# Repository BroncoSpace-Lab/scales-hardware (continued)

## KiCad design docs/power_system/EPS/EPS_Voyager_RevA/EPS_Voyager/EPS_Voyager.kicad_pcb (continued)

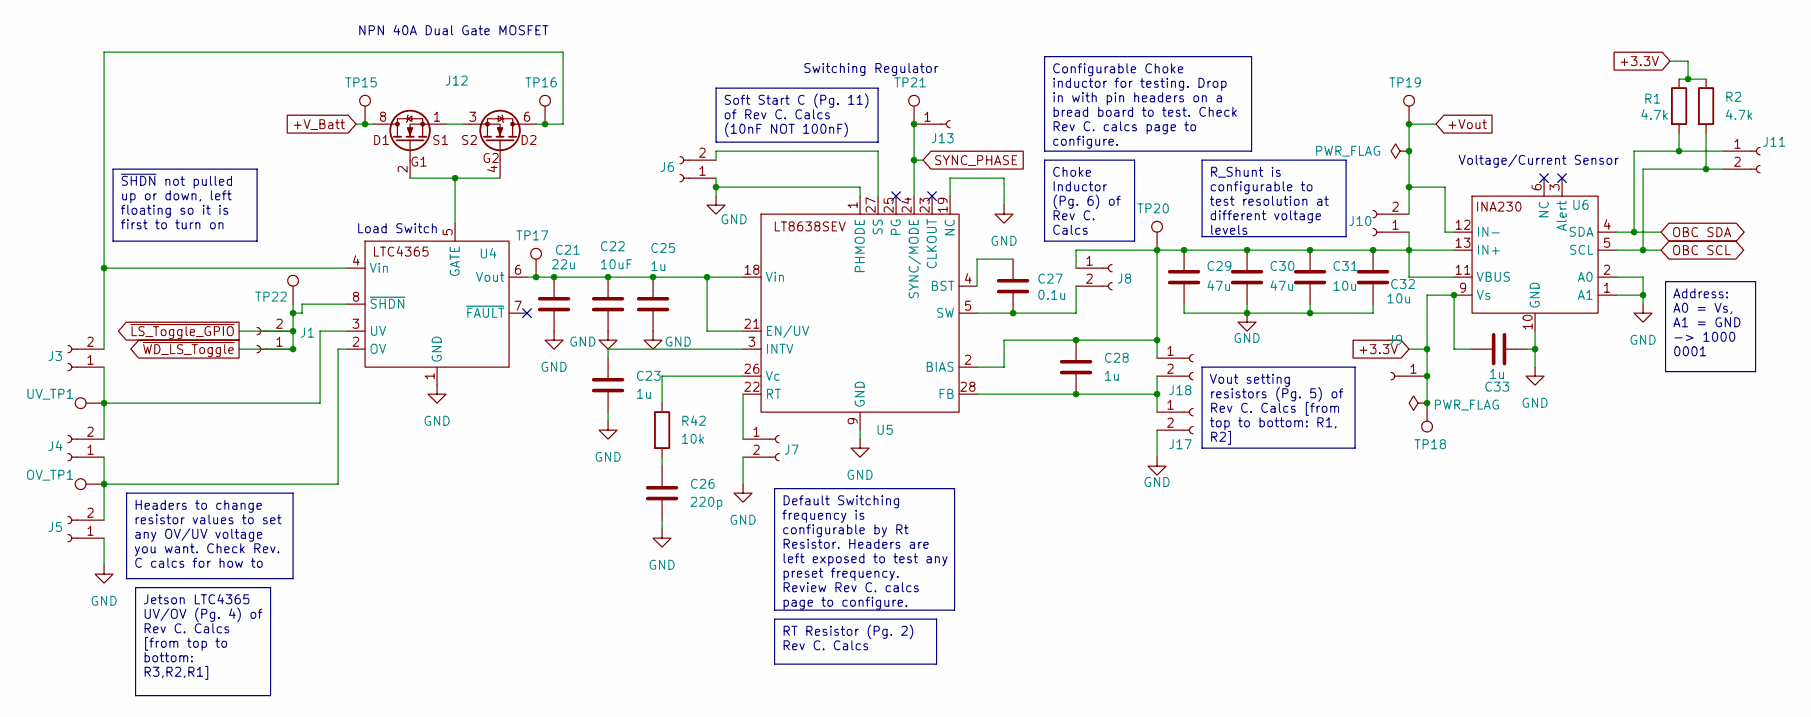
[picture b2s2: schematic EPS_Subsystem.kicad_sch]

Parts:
C21: 22u; C_1210_3225Metric
C22: 10uF; C_1210_3225Metric
C23, C25, C28, C33: 1u; C_1210_3225Metric
C26: 220p; C_1210_3225Metric
C27: 0.1u; C_1210_3225Metric
C29, C30: 47u; C_1210_3225Metric
C31, C32: 10u; C_1210_3225Metric
J1, J3, J4, J5, J6, J7, J8, J10, J11, J17, J18: Conn_01x02_Socket; PinSocket_1x02_P2.54mm_Vertical
J9, J13: Conn_01x01_Socket; PinSocket_1x01_P2.54mm_Vertical
J12: SISB46DN-T1-GE3
OV_TP1: TestPoint; TestPoint_Pad_1.0x1.0mm
R1, R2: 4.7k; R_0603_1608Metric
R42: 10k; R_0603_1608Metric
TP15, TP16, TP17, TP18, TP19, TP20, TP21, TP22: TestPoint; TestPoint_Pad_1.0x1.0mm
U4: LTC4365
U5: LT8638SEVPBF
U6: INA230; INA230AIRGTT
UV_TP1: TestPoint; TestPoint_Pad_1.0x1.0mm

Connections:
+3.3V: C33.2, J9.1, R1.1, R2.1, TP18.1, U6.9 (Vs); also elsewhere on the board
+V_Batt: J12.7, J12.8, TP15.1; also elsewhere on the board
+Vout: J10.2, TP19.1, U6.12 (IN-)
GND: C21.2, C22.2, C23.2, C25.2, C26.2, C29.2, C30.2, C31.2, C32.2, C33.1, J5.1, J6.1, J7.2, J17.2, U4.1 (GND), U5.1 (PHMODE), U5.9 (GND), U5.19 (NC), U6.1 (A1), U6.2 (A0), U6.10 (GND); also elsewhere on the board
unnamed: C26.1, R42.2
unnamed: J3.1, J4.2, U4.3 (UV), UV_TP1.1
unnamed: J3.2, J12.5, J12.6, TP16.1, U4.4 (Vin)
unnamed: J4.1, J5.2, OV_TP1.1, U4.2 (OV)
unnamed: J6.2, U5.27 (SS)
unnamed: J7.1, U5.22 (RT)
unnamed: C27.2, J8.2, U5.5 (SW)
unnamed: C28.1, C29.1, C30.1, C31.1, C32.1, J8.1, J10.1, J18.1, TP20.1, U5.2 (BIAS), U6.11 (VBUS), U6.13 (IN+)
unnamed: J12.1, J12.3
unnamed: C28.2, J17.1, J18.2, U5.28 (FB)
unnamed: J12.2, J12.4, U4.5 (GATE)
unnamed: C21.1, C22.1, C25.1, TP17.1, U4.6 (Vout), U5.18 (Vin), U5.21 (EN/UV)
unnamed: C27.1, U5.4 (BST)
unnamed: C23.1, U5.3 (INTV)
unnamed: R42.1, U5.26 (Vc)
OBC SCL: J11.2, R2.2, U6.5 (SCL)
OBC SDA: J11.1, R1.2, U6.4 (SDA)
SYNC_PHASE: J13.1, TP21.1, U5.24 (SYNC/MODE)
~LS_Toggle_GPIO: J1.1, J1.2, TP22.1, U4.8 (~SHDN)

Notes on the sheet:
Switching Regulator
NPN 40A Dual Gate MOSFET
Voltage/Current Sensor
Load Switch
RT Resistor (Pg. 2) Rev C. Calcs
Soft Start C (Pg. 11) of Rev C. Calcs (10nF NOT 100nF)
Headers to change resistor values to set any OV/UV voltage you want. Check Rev. C calcs for how to
R_Shunt is configurable to test resolution at different voltage levels
Configurable Choke inductor for testing. Drop in with pin headers on a bread board to test. Check Rev C. calcs page to configure.
Address: A0 = Vs, A1 = GND -> 1000 0001
Vout setting resistors (Pg. 5) of Rev C. Calcs [from top to bottom: R1, R2]
Choke Inductor (Pg. 6) of Rev C. Calcs
Jetson LTC4365 UV/OV (Pg. 4) of Rev C. Calcs [from top to bottom: R3,R2,R1]
~{SHDN} not pulled up or down, left floating so it is first to turn on
Default Switching frequency is configurable by Rt Resistor. Headers are left exposed to test any preset frequency. Review Rev C. calcs page to configure.

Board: 4 copper layers, 52 parts (0 on the bottom side), 29 nets, no tracks yet.

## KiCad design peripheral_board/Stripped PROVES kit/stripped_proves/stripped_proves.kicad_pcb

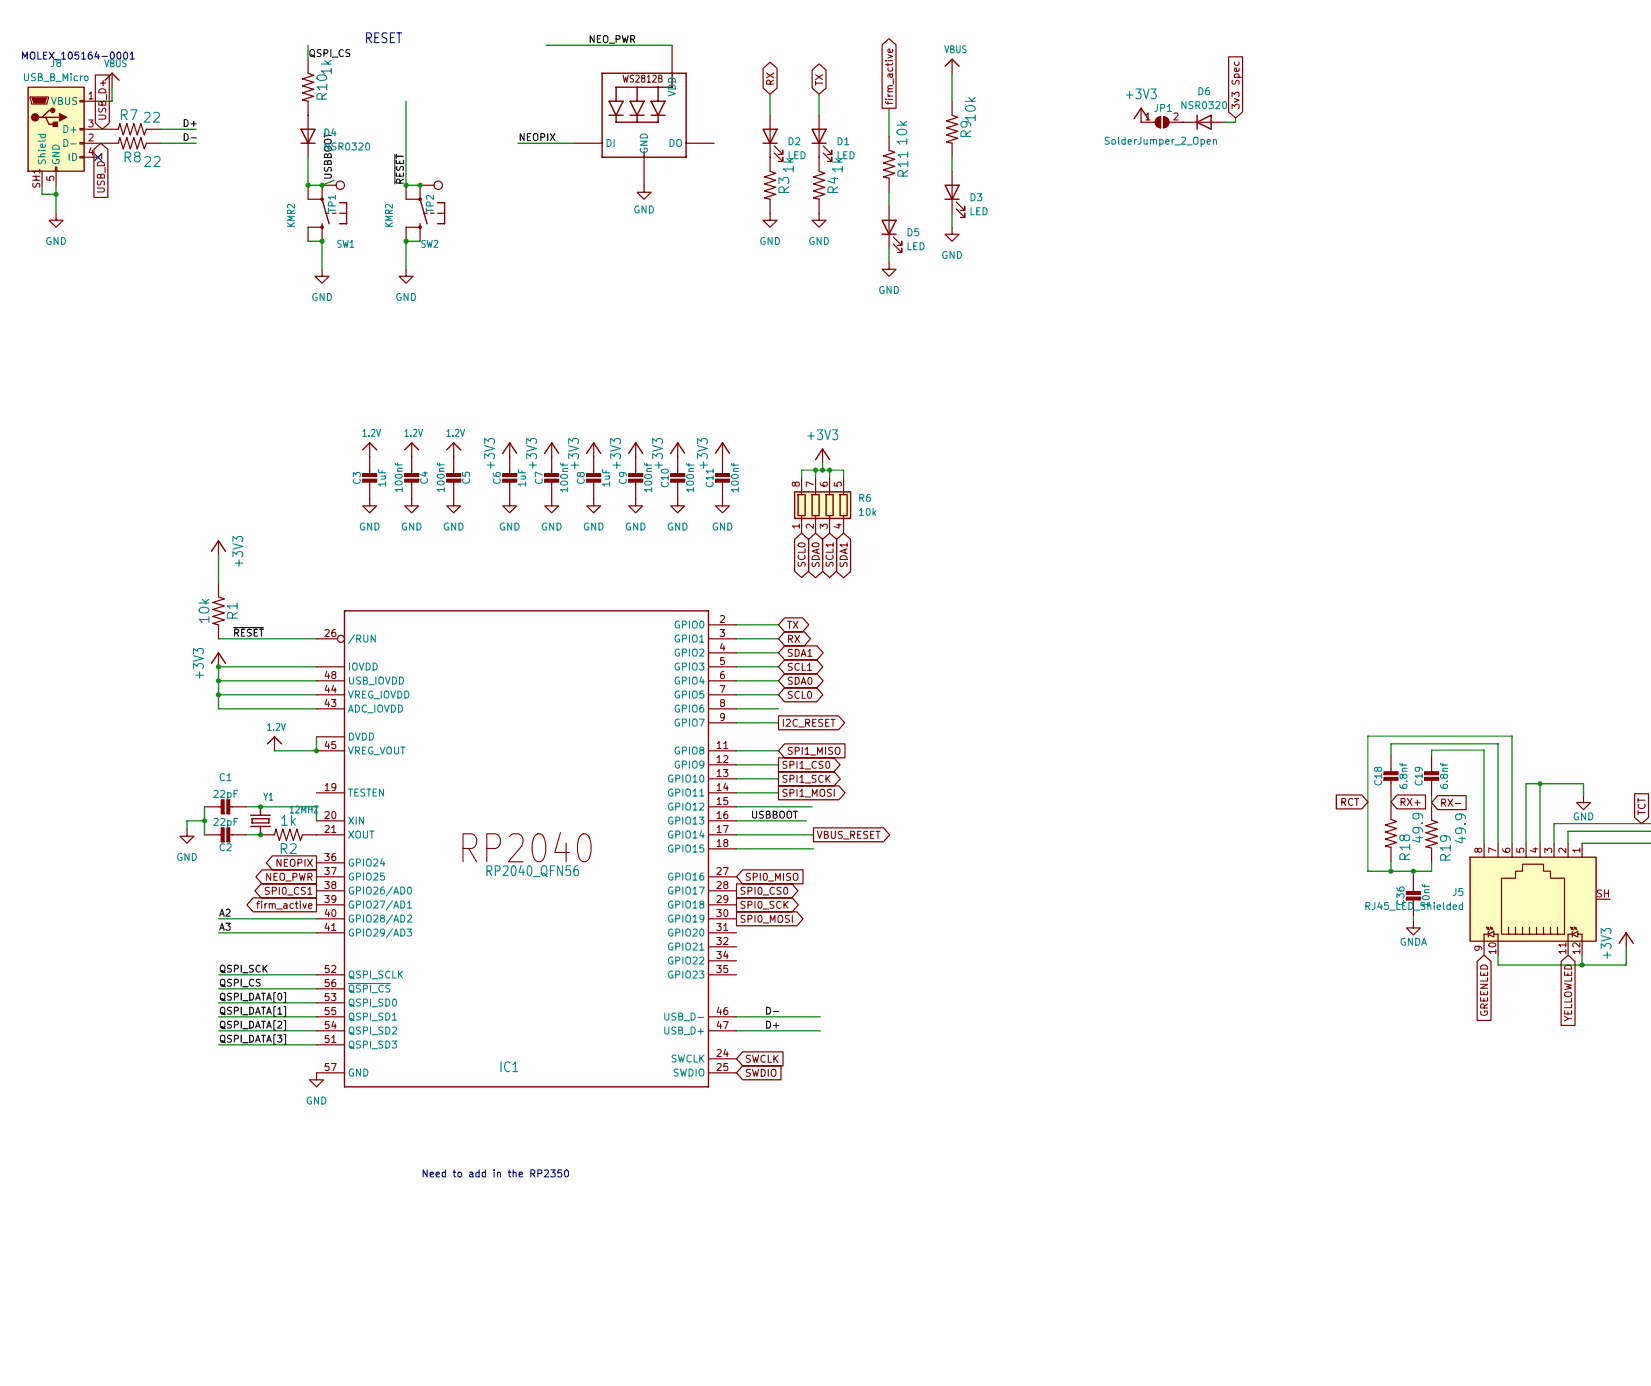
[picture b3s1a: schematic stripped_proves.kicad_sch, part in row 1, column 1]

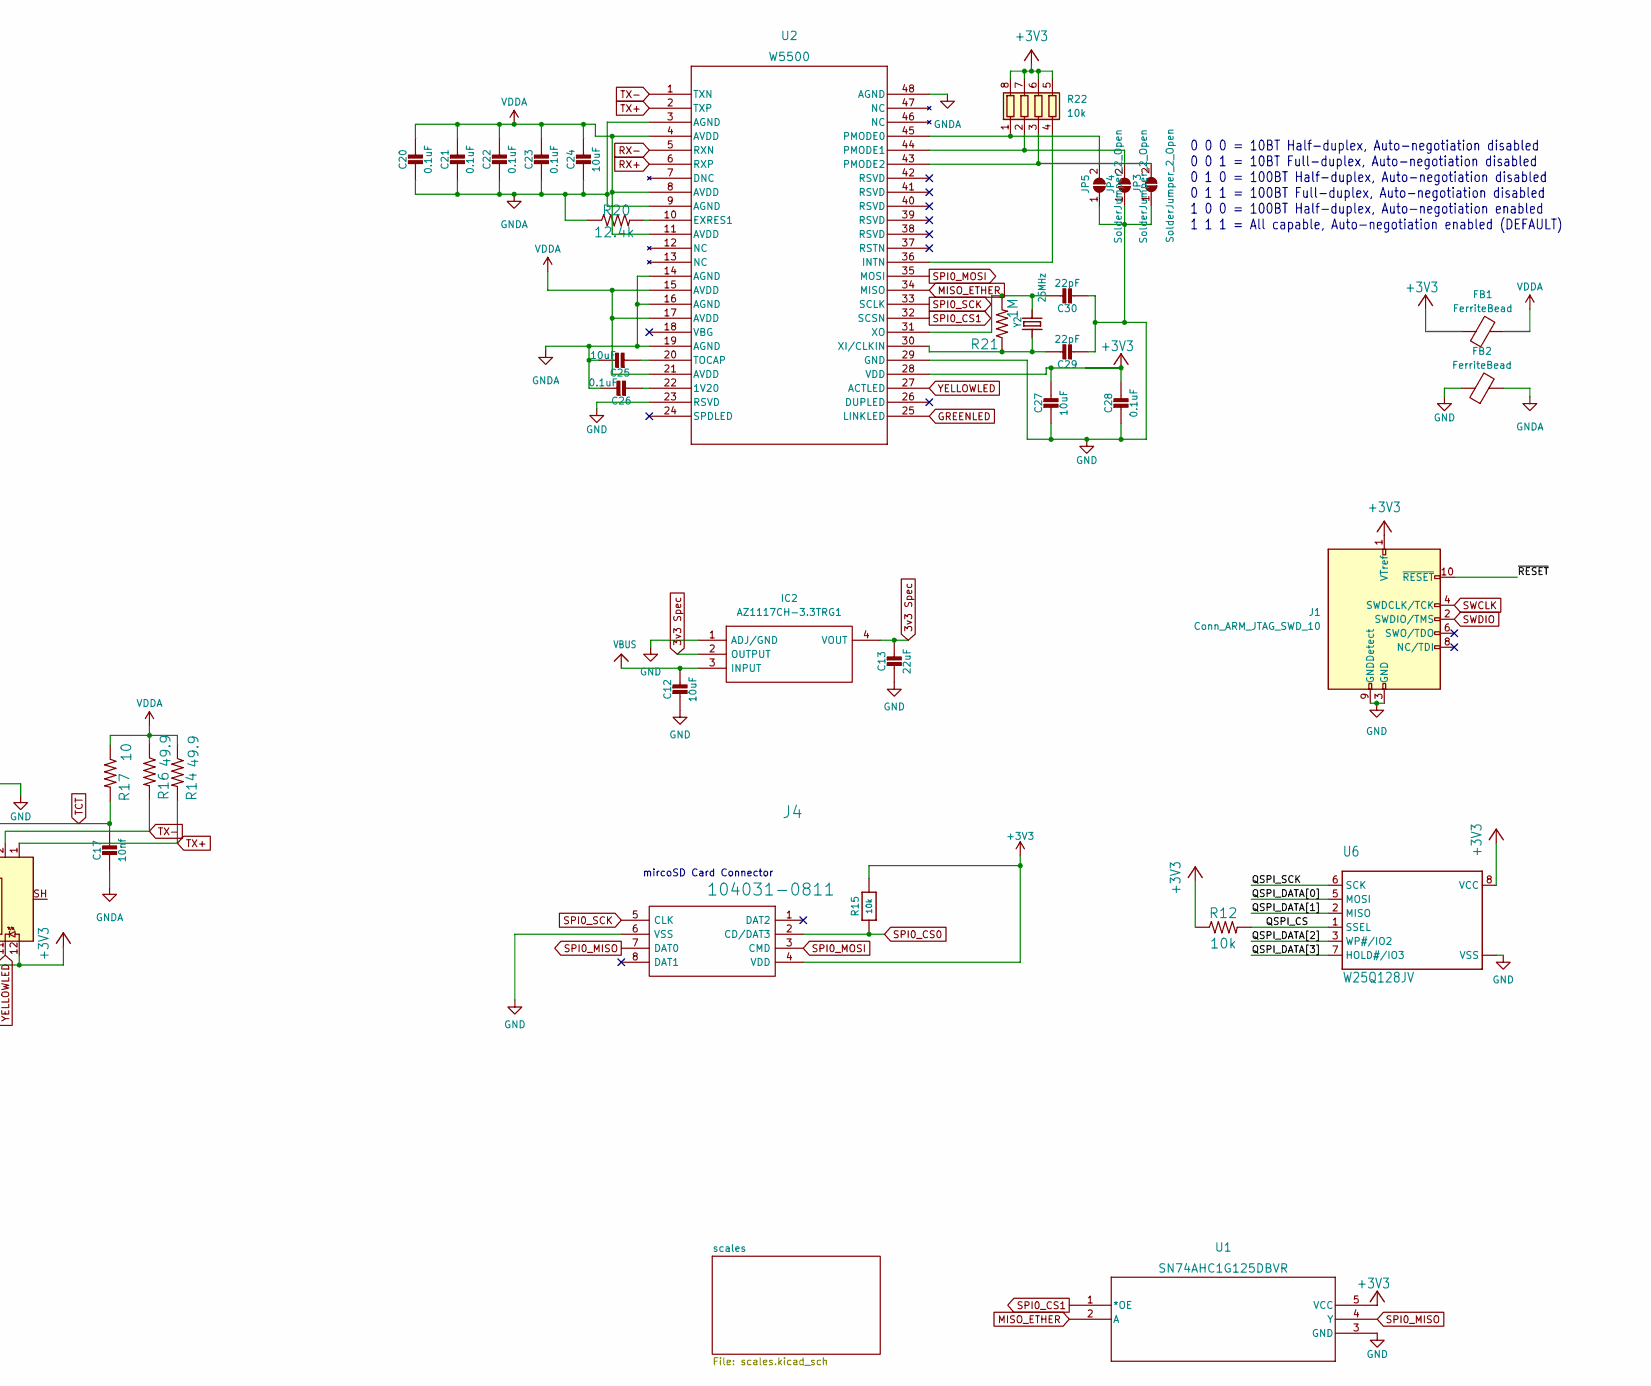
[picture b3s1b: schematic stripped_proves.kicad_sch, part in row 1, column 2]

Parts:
C1, C2, C29, C30: 22pF; C_0402_1005Metric
C3, C6, C8: 1uF; C_0603_1608Metric
C4, C5, C7, C9, C10, C11: 100nf; C_0402_1005Metric
C12: 10uF; C_0603_1608Metric
C13: 22uF; C_0603_1608Metric
C17, C36: 10nf; C_0402_1005Metric
C18, C19: 6.8nf; C_0402_1005Metric
C20, C21, C22, C23, C26, C28: 0.1uF; C_0603_1608Metric
C24, C25, C27: 10uF; C_0805_2012Metric
D1, D2, D3, D5: LED; LED_0603_1608Metric
D4, D6: NSR0320; D_SOD-323F
FB1, FB2: FerriteBead; R_0603_1608Metric
IC1: RP2040_QFN56; QFN-56-1EP_7x7mm_P0.4mm_EP3.2x3.2mm_ThermalVias
IC2: AZ1117CH-3.3TRG1; SOT-223; Mouser Part Number 621-AZ1117CH-3.3TRG1
J1: Conn_ARM_JTAG_SWD_10; JTAG_2X05_1.27MM_BOX_NOCREAM
J4: 104031-0811; microSD_HC_Molex_104031-0811; Manufacturer_Part_Number 104031-0811; Mouser Part Number 538-104031-0811
J5: RJ45_LED_Shielded; RB1-125BAG1A_WIZ
J8: USB_B_Micro; MOLEX_105164-0001
JP1, JP3, JP4, JP5: SolderJumper_2_Open; SolderJumper-2_P1.3mm_Open_RoundedPad1.0x1.5mm
LED1: WS2812B_SK6812_1515; LED_WS2812B_PLCC4_5.0x5.0mm_P3.2mm
R1, R9, R11, R12: 10k; R_0603_1608Metric
R2: 1k; R_0402_1005Metric
R3, R4, R10: 1k; R_0603_1608Metric
R6, R22: 10k; R_Array_Convex_4x0603
R7, R8: 22; R_0603_1608Metric
R14, R16, R18, R19: 49.9; R_0603_1608Metric
R15: 10k; R_0402_1005Metric
R17: 10; R_0603_1608Metric
R20: 12.4k; R_0603_1608Metric
R21: 1M; R_0603_1608Metric
SW1, SW2: KMR2; BTN_KMR2_4.6X2.8
TP1: USBBOOT; TestPoint_Loop_D1.80mm_Drill1.0mm_Beaded
TP2: RESET; TestPoint_Loop_D1.80mm_Drill1.0mm_Beaded
U1: SN74AHC1G125DBVR; SOT-23-5
U2: W5500; LQFP-48_7x7mm_P0.5mm
U6: W25Q128JV; SOIC-8_5.275x5.275mm_P1.27mm
Y1: 12MHZ; Crystal_SMD_2520-4Pin_2.5x2.0mm
Y2: 25MHz; Crystal_SMD_3225-4Pin_3.2x2.5mm

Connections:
1.2V: C3.1, C4.2, C5.2, IC1.23 (DVDD), IC1.45 (VREG_VOUT), IC1.50 (DVDD)
3v3 Spec: C13.1, D6.2 (A), IC2.2 (OUTPUT), IC2.4 (VOUT)
+3V3: C6.1, C7.1, C8.1, C9.1, C10.1, C11.1, C27.1, C28.1, FB1.1, IC1.1 (IOVDD), IC1.10 (IOVDD), IC1.22 (IOVDD), IC1.33 (IOVDD), IC1.42 (IOVDD), IC1.43 (ADC_IOVDD), IC1.44 (VREG_IOVDD), IC1.48 (USB_IOVDD), IC1.49 (IOVDD), J1.1 (VTref), J4.4 (VDD), J5.10, J5.12, JP1.1 (A), R1.1, R6.5 (R4.2), R6.6 (R3.2), R6.7 (R2.2), R6.8 (R1.2), R12.1, R15.2, R22.5 (R4.2), R22.6 (R3.2), R22.7 (R2.2), R22.8 (R1.2), U1.5 (VCC), U2.28 (VDD), U6.8 (VCC); also elsewhere on the board
/A2: IC1.40 (GPIO28/AD2)
/A3: IC1.41 (GPIO29/AD3)
/D+: IC1.47 (USB_D+), R7.1
/D-: IC1.46 (USB_D-), R8.1
/QSPI_CS: IC1.56 (~QSPI_CS), R10.1, R12.2, U6.1 (SSEL)
/QSPI_DATA[0]: IC1.53 (QSPI_SD0), U6.5 (MOSI)
/QSPI_DATA[1]: IC1.55 (QSPI_SD1), U6.2 (MISO)
/QSPI_DATA[2]: IC1.54 (QSPI_SD2), U6.3 (WP#/IO2)
/QSPI_DATA[3]: IC1.51 (QSPI_SD3), U6.7 (HOLD#/IO3)
/QSPI_SCK: IC1.52 (QSPI_SCLK), U6.6 (SCK)
/USBBOOT: D4.1 (K), IC1.16 (GPIO13), SW1.A, SW1.A' (P1), TP1.1
/~RESET: IC1.26 (/RUN), J1.10 (~RESET), R1.2, SW2.A, SW2.A' (P1), TP2.1
EN_1.2V: C12.1, IC2.3 (INPUT), J8.1 (VBUS), R9.1; also elsewhere on the board
GND: C1.1, C2.1, C3.2, C4.1, C5.1, C6.2, C7.2, C8.2, C9.2, C10.2, C11.2, C12.2, C13.2, C27.2, C28.2, C29.2, C30.2, D3.1 (K), D5.1 (K), FB2.1, IC1.57 (GND), IC2.1 (ADJ/GND), J1.3 (GND), J1.5 (GND), J1.9 (GNDDetect), J4.6 (VSS), J5.4, J5.5, J8.5 (GND), J8.SH1 (Shield), LED1.3 (GND), R3.2, R4.2, SW1.B (S), SW1.B' (S1), SW2.B (S), SW2.B' (S1), U1.3 (GND), U2.23 (RSVD), U2.29 (GND), U6.4 (VSS), U6.PAD (VSS); also elsewhere on the board
GNDA: C17.2, C20.2, C21.2, C22.2, C23.2, C24.2, C25.1, C26.1, C36.2, FB2.2, R20.1, U2.3 (AGND), U2.9 (AGND), U2.14 (AGND), U2.16 (AGND), U2.19 (AGND), U2.48 (AGND)
GREENLED: J5.9, U2.25 (LINKLED)
I2C_RESET: IC1.9 (GPIO7)
MISO_ETHER: U1.2 (A), U2.34 (MISO)
NEOPIX: IC1.36 (GPIO24), LED1.4 (DI)
NEO_PWR: IC1.37 (GPIO25), LED1.1 (VDD)
unnamed: C2.2, R2.2, Y1.1
unnamed: C18.1, J5.7
unnamed: C19.1, J5.8
unnamed: D1.1 (K), R4.1
unnamed: D2.1 (K), R3.1
unnamed: D3.2 (A), R9.2
unnamed: D4.2 (A), R10.2
unnamed: D5.2 (A), R11.2
unnamed: D6.1 (K), JP1.2 (B)
unnamed: C1.2, IC1.20 (XIN), Y1.3 (2)
unnamed: IC1.21 (XOUT), R2.1
unnamed: JP3.1 (A), JP4.1 (A), JP5.1 (A)
unnamed: JP3.2 (B), R22.3 (R3.1), U2.43 (PMODE2)
unnamed: JP4.2 (B), R22.2 (R2.1), U2.44 (PMODE1)
unnamed: JP5.2 (B), R22.1 (R1.1), U2.45 (PMODE0)
unnamed: R22.4 (R4.1), U2.36 (INTN)
unnamed: C26.2, U2.22 (1V20)
unnamed: R20.2, U2.10 (EXRES1)
unnamed: C25.2, U2.20 (TOCAP)
unnamed: C29.1, R21.1, U2.30 (XI/CLKIN), Y2.1
unnamed: C30.1, R21.2, U2.31 (XO), Y2.3 (2)
RCT: C36.1, J5.6, R18.2, R19.2
RX: D2.2 (A), IC1.3 (GPIO1)
RX+: C18.2, R18.1, U2.6 (RXP)
RX-: C19.2, R19.1, U2.5 (RXN)
SCL0: IC1.7 (GPIO5), R6.1 (R1.1)
SCL1: IC1.5 (GPIO3), R6.3 (R3.1)
SDA0: IC1.6 (GPIO4), R6.2 (R2.1)
SDA1: IC1.4 (GPIO2), R6.4 (R4.1)
SPI0_CS0: IC1.28 (GPIO17), J4.2 (CD/DAT3), R15.1
SPI0_CS1: IC1.38 (GPIO26/AD0), U1.1 (*OE), U2.32 (SCSN)
SPI0_MISO: IC1.27 (GPIO16), J4.7 (DAT0), U1.4 (Y)
SPI0_MOSI: IC1.30 (GPIO19), J4.3 (CMD), U2.35 (MOSI)
SPI0_SCK: IC1.29 (GPIO18), J4.5 (CLK), U2.33 (SCLK)
SPI1_CS0: IC1.12 (GPIO9)
SPI1_MISO: IC1.11 (GPIO8)
SPI1_MOSI: IC1.14 (GPIO11)
SPI1_SCK: IC1.13 (GPIO10)
SWCLK: IC1.24 (SWCLK), J1.4 (SWDCLK/TCK)
SWDIO: IC1.25 (SWDIO), J1.2 (SWDIO/TMS)
TCT: C17.1, J5.3, R17.2
TX: D1.2 (A), IC1.2 (GPIO0)
TX+: J5.1, R14.2, U2.2 (TXP)
TX-: J5.2, R16.2, U2.1 (TXN)
USB_D+: J8.3 (D+), R7.2
USB_D-: J8.2 (D-), R8.2
VBUS_RESET: IC1.17 (GPIO14)
VDDA: C20.1, C21.1, C22.1, C23.1, C24.1, FB1.2, R14.1, R16.1, R17.1, U2.4 (AVDD), U2.8 (AVDD), U2.11 (AVDD), U2.15 (AVDD), U2.17 (AVDD), U2.21 (AVDD)
YELLOWLED: J5.11, U2.27 (ACTLED)
firm_active: IC1.39 (GPIO27/AD1), R11.1

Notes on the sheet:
0 0 0 = 10BT Half-duplex, Auto-negotiation disabled 0 0 1 = 10BT Full-duplex, Auto-negotiation disabled 0 1 0 = 100BT Half-duplex, Auto-negotiation disabled 0 1 1 = 100BT Full-duplex, Auto-negotiation disabled 1 0 0 = 100BT Half-duplex, Auto-negotiation enabled 1 1 1 = All capable, Auto-negotiation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
mircoSD Card Connector
MOLEX_105164-0001
RESET
Need to add in the RP2350

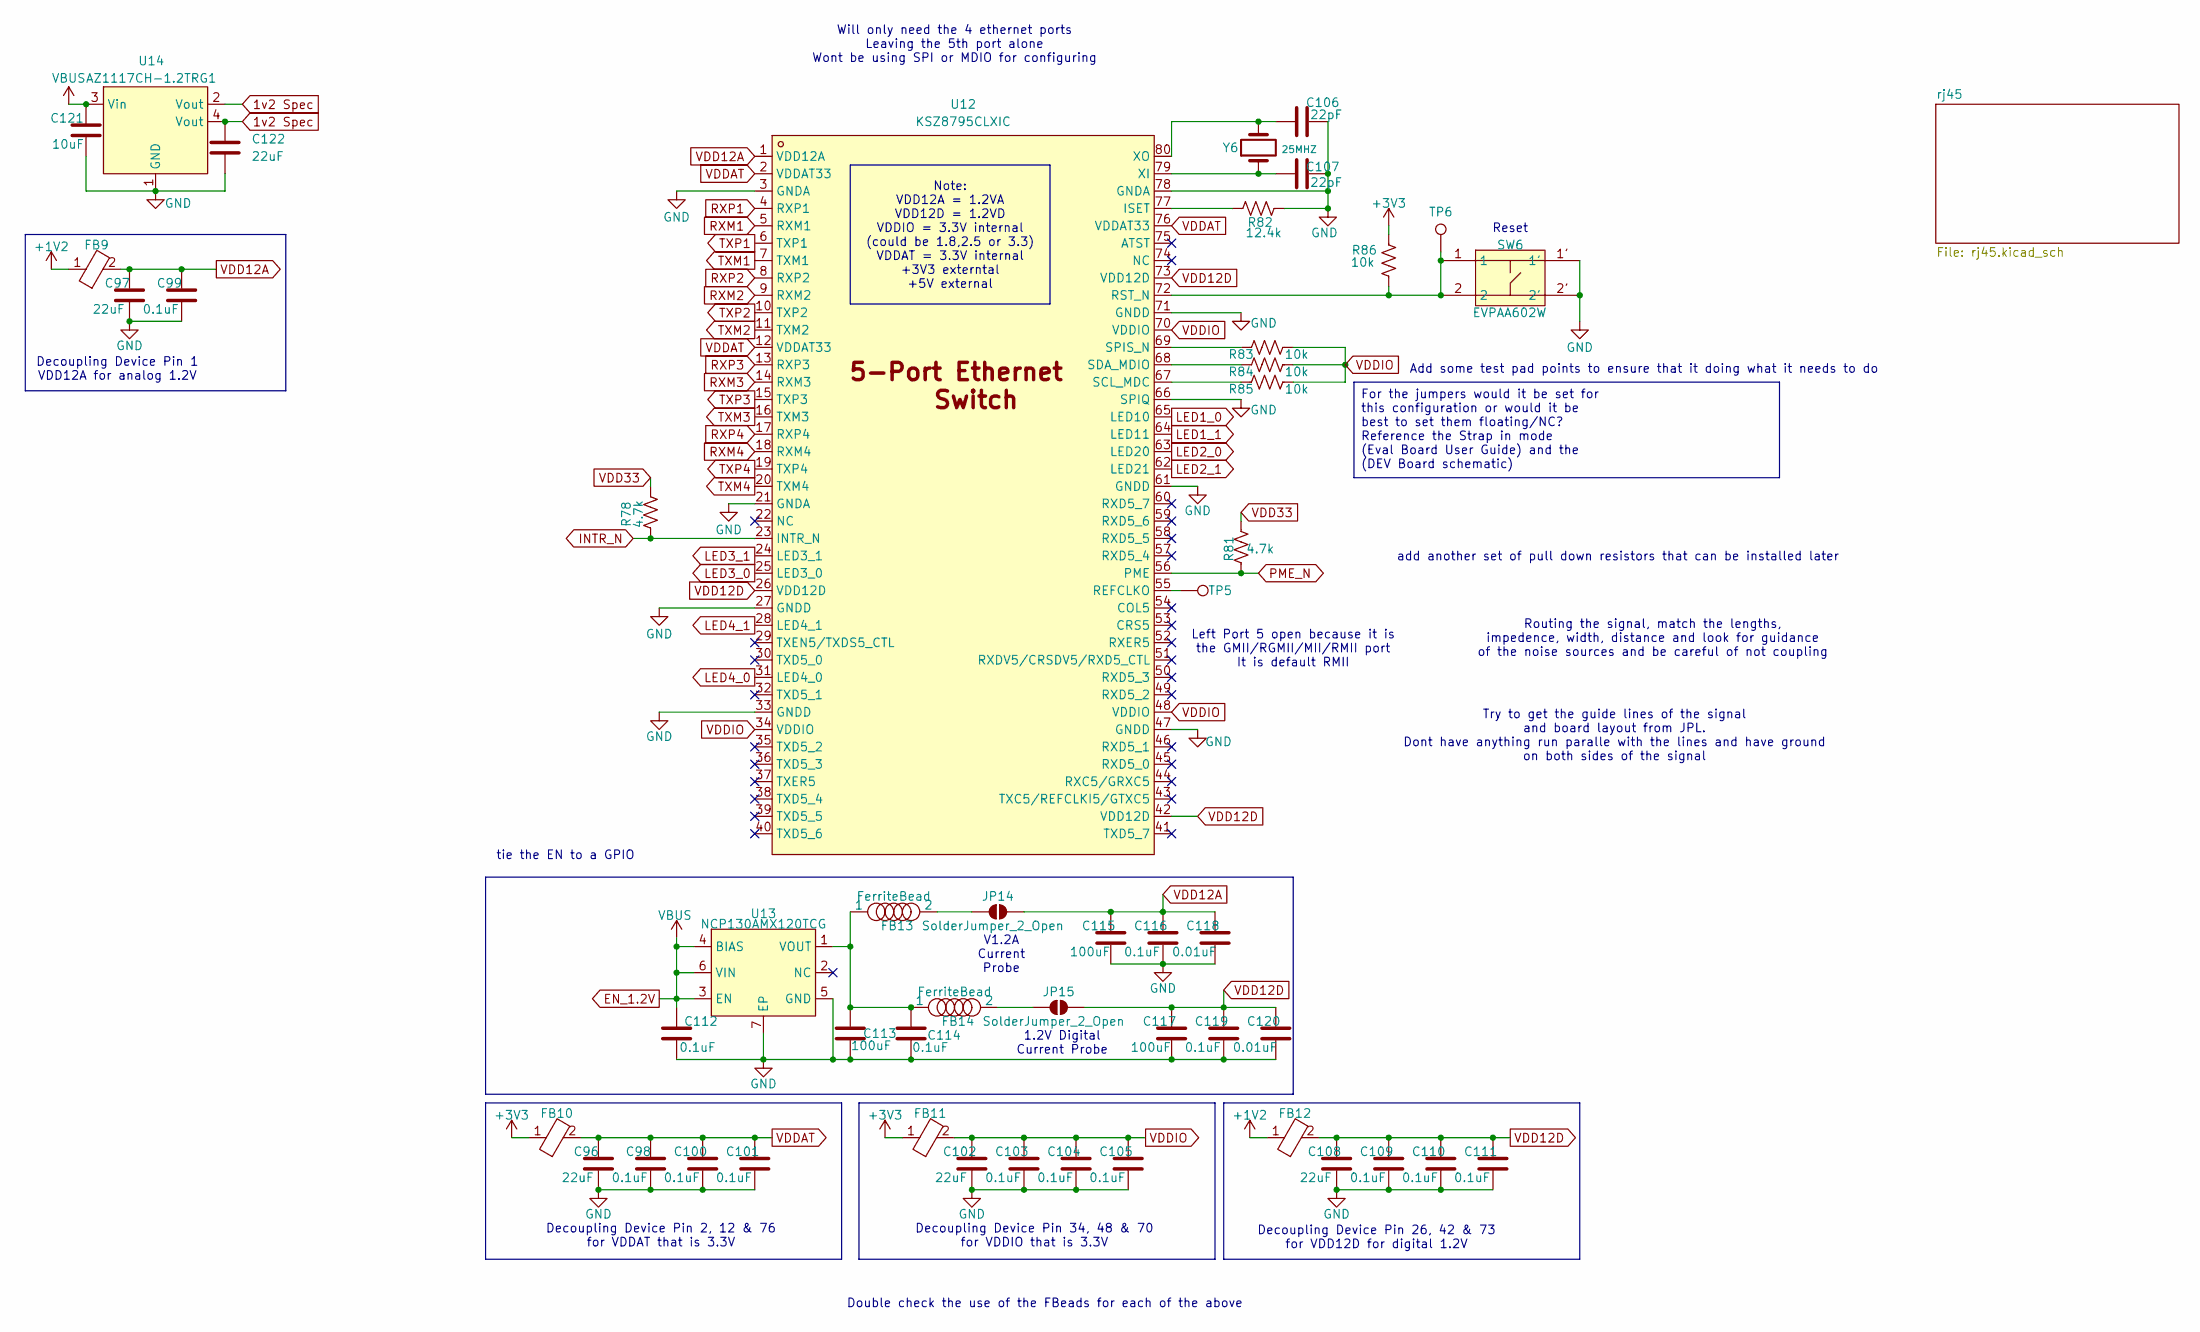
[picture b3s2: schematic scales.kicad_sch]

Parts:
C96, C97, C102, C108, C122: 22uF; C_0402_1005Metric
C98, C99, C100, C101, C103, C104, C105, C109, C110, C111, C112, C114, C116, C119: 0.1uF; C_0402_1005Metric
C106, C107: 22pF; C_0402_1005Metric
C113, C115, C117: 100uF; C_0402_1005Metric
C118, C120: 0.01uF; C_0402_1005Metric
C121: 10uF; C_0402_1005Metric
FB9, FB10, FB11, FB12: CBW321609U101T; L1206; LCSC Part C91466
FB13, FB14: FerriteBead; L_0603_1608Metric
JP14, JP15: SolderJumper_2_Open; SolderJumper-2_P1.3mm_Open_RoundedPad1.0x1.5mm
R78, R81: 4.7k; R_0603_1608Metric
R82: 12.4k; R_0603_1608Metric
R83, R84, R85, R86: 10k; R_0603_1608Metric
SW6: EVPAA602W; KEY-TH_4P-L3.5-W4.9-P2.80-LS4.3; LCSC Part C79148
TP5, TP6: TestPoint; TestPoint_Pad_1.0x1.0mm
U12: KSZ8795CLXIC; LQFP-80_L10.0-W10.0-P0.40-LS12.2-BL; LCSC Part C69416
U13: NCP130AMX120TCG; XDFN-6_L1.2-W1.2-P0.40-BL-EP; LCSC Part C892096
U14: AZ1117CH-1.2TRG1; SOT-223-3_L6.5-W3.4-P2.30-LS7.0-BR; LCSC Part C507895
Y6: 25MHZ; Crystal_SMD_2012-2Pin_2.0x1.2mm

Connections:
1v2 Spec: C122.2, U14.2 (Vout), U14.4 (Vout)
+1V2: FB9.1, FB12.1
+3V3: FB10.1, FB11.1, R86.1; also elsewhere on the board
EN_1.2V: C112.2, C121.2, U13.3 (EN), U13.4 (BIAS), U13.6 (VIN), U14.3 (Vin); also elsewhere on the board
GND: C96.1, C97.1, C98.1, C99.1, C100.1, C101.1, C102.1, C103.1, C104.1, C105.1, C106.2, C107.2, C108.1, C109.1, C110.1, C111.1, C112.1, C113.1, C114.1, C115.1, C116.1, C117.1, C118.1, C119.1, C120.1, C121.1, C122.1, R82.2, SW6.1', SW6.2', U12.3 (GNDA), U12.21 (GNDA), U12.27 (GNDD), U12.33 (GNDD), U12.47 (GNDD), U12.61 (GNDD), U12.66 (SPIQ), U12.71 (GNDD), U12.78 (GNDA), U13.5 (GND), U13.7 (EP), U14.1 (GND); also elsewhere on the board
INTR_N: R78.2, U12.23 (INTR_N)
LED1_0: U12.65 (LED10)
LED1_1: U12.64 (LED11)
LED2_0: U12.63 (LED20)
LED2_1: U12.62 (LED21)
LED3_0: U12.25 (LED3_0)
LED3_1: U12.24 (LED3_1)
LED4_0: U12.31 (LED4_0)
LED4_1: U12.28 (LED4_1)
unnamed: FB13.2, JP14.2 (B)
unnamed: FB14.2, JP15.2 (B)
unnamed: R82.1, U12.77 (ISET)
unnamed: TP5.1, U12.55 (REFCLKO)
unnamed: R86.2, SW6.1, SW6.2, TP6.1, U12.72 (RST_N)
unnamed: R85.1, U12.67 (SCL_MDC)
unnamed: R84.1, U12.68 (SDA_MDIO)
unnamed: R83.1, U12.69 (SPIS_N)
unnamed: C107.1, U12.79 (XI), Y6.1
unnamed: C106.1, U12.80 (XO), Y6.2
unnamed: C113.2, C114.2, FB13.1, FB14.1, U13.1 (VOUT)
PME_N: R81.2, U12.56 (PME)
RXM1: U12.5 (RXM1)
RXM2: U12.9 (RXM2)
RXM3: U12.14 (RXM3)
RXM4: U12.18 (RXM4)
RXP1: U12.4 (RXP1)
RXP2: U12.8 (RXP2)
RXP3: U12.13 (RXP3)
RXP4: U12.17 (RXP4)
TXM1: U12.7 (TXM1)
TXM2: U12.11 (TXM2)
TXM3: U12.16 (TXM3)
TXM4: U12.20 (TXM4)
TXP1: U12.6 (TXP1)
TXP2: U12.10 (TXP2)
TXP3: U12.15 (TXP3)
TXP4: U12.19 (TXP4)
VDD12A: C97.2, C99.2, C115.2, C116.2, C118.2, FB9.2, JP14.1 (A), U12.1 (VDD12A)
VDD12D: C108.2, C109.2, C110.2, C111.2, C117.2, C119.2, C120.2, FB12.2, JP15.1 (A), U12.26 (VDD12D), U12.42 (VDD12D), U12.73 (VDD12D)
VDD33: R78.1, R81.1
VDDAT: C96.2, C98.2, C100.2, C101.2, FB10.2, U12.2 (VDDAT33), U12.12 (VDDAT33), U12.76 (VDDAT33)
VDDIO: C102.2, C103.2, C104.2, C105.2, FB11.2, R83.2, R84.2, R85.2, U12.34 (VDDIO), U12.48 (VDDIO), U12.70 (VDDIO)

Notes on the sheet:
Routing the signal, match the lengths, impedence, width, distance and look for guidance of the noise sources and be careful of not coupling
Double check the use of the FBeads for each of the above
Decoupling Device Pin 26, 42 & 73 for VDD12D for digital 1.2V
Left Port 5 open because it is the GMII/RGMII/MII/RMII port It is default RMII
Reset
Try to get the guide lines of the signal and board layout from JPL. Dont have anything run paralle with the lines and have ground on both sides of the signal
Decoupling Device Pin 2, 12 & 76 for VDDAT that is 3.3V
Decoupling Device Pin 34, 48 & 70 for VDDIO that is 3.3V
tie the EN to a GPIO
1.2V Digital Current Probe
add another set of pull down resistors that can be installed later
Decoupling Device Pin 1 VDD12A for analog 1.2V
Add some test pad points to ensure that it doing what it needs to do
Will only need the 4 ethernet ports Leaving the 5th port alone Wont be using SPI or MDIO for configuring
V1.2A Current Probe
Note: VDD12A = 1.2VA VDD12D = 1.2VD VDDIO = 3.3V internal (could be 1.8,2.5 or 3.3) VDDAT = 3.3V internal +3V3 externtal +5V external
For the jumpers would it be set for this configuration or would it be best to set them floating/NC? Reference the Strap in mode (Eval Board User Guide) and the (DEV Board schematic)

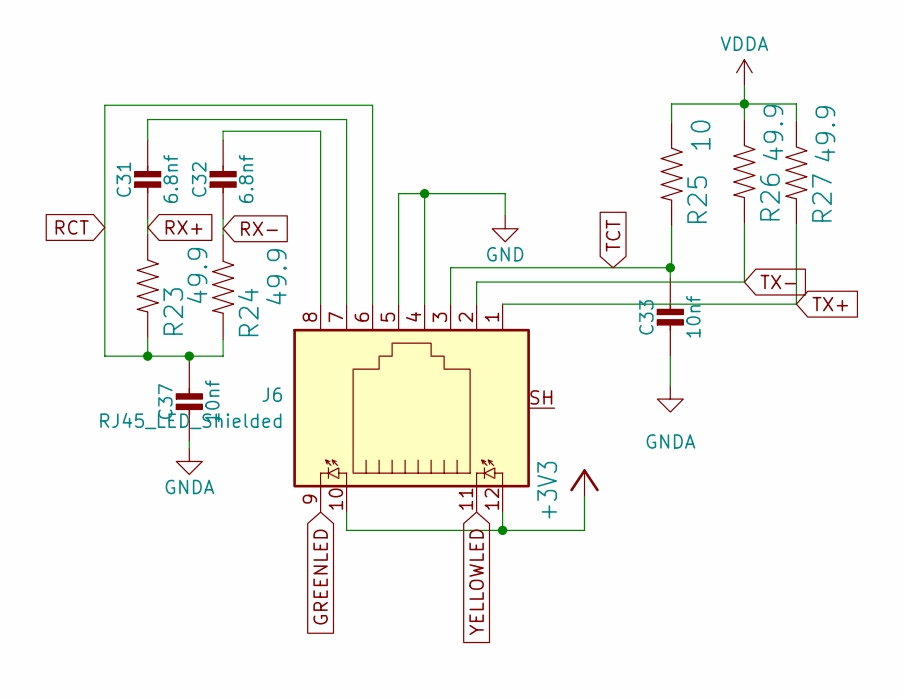
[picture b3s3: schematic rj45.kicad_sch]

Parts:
C31, C32: 6.8nf; C_0402_1005Metric
C33, C37: 10nf; C_0402_1005Metric
J6: RJ45_LED_Shielded; RB1-125BAG1A_WIZ
R23, R24, R26, R27: 49.9; R_0603_1608Metric
R25: 10; R_0603_1608Metric

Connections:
unnamed: C31.1, J6.7
unnamed: C31.2, R23.1
unnamed: C32.1, J6.8
unnamed: C32.2, R24.1
unnamed: C33.1, J6.3, R25.2
unnamed: C33.2, C37.2
unnamed: C37.1, J6.6, R23.2, R24.2
unnamed: J6.1, R27.2
unnamed: J6.2, R26.2
unnamed: J6.4, J6.5
unnamed: J6.10, J6.12
unnamed: R25.1, R26.1, R27.1

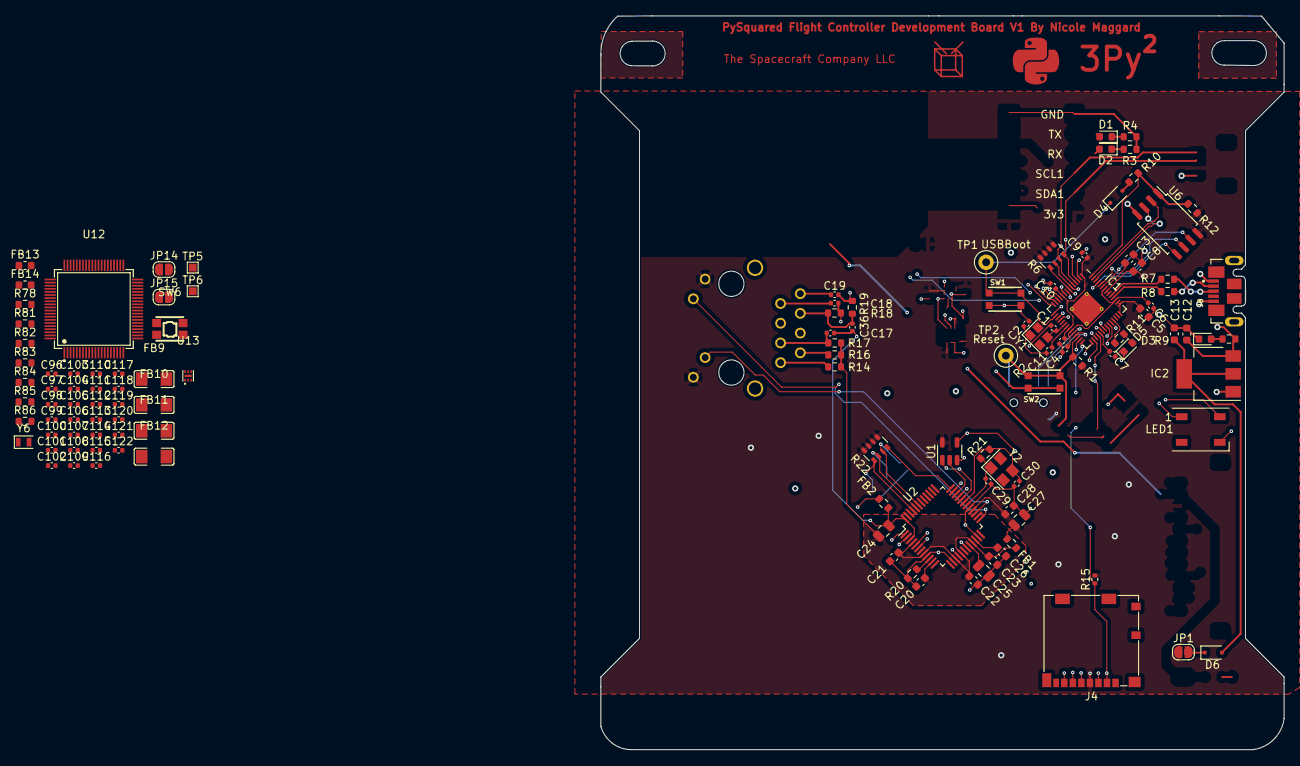
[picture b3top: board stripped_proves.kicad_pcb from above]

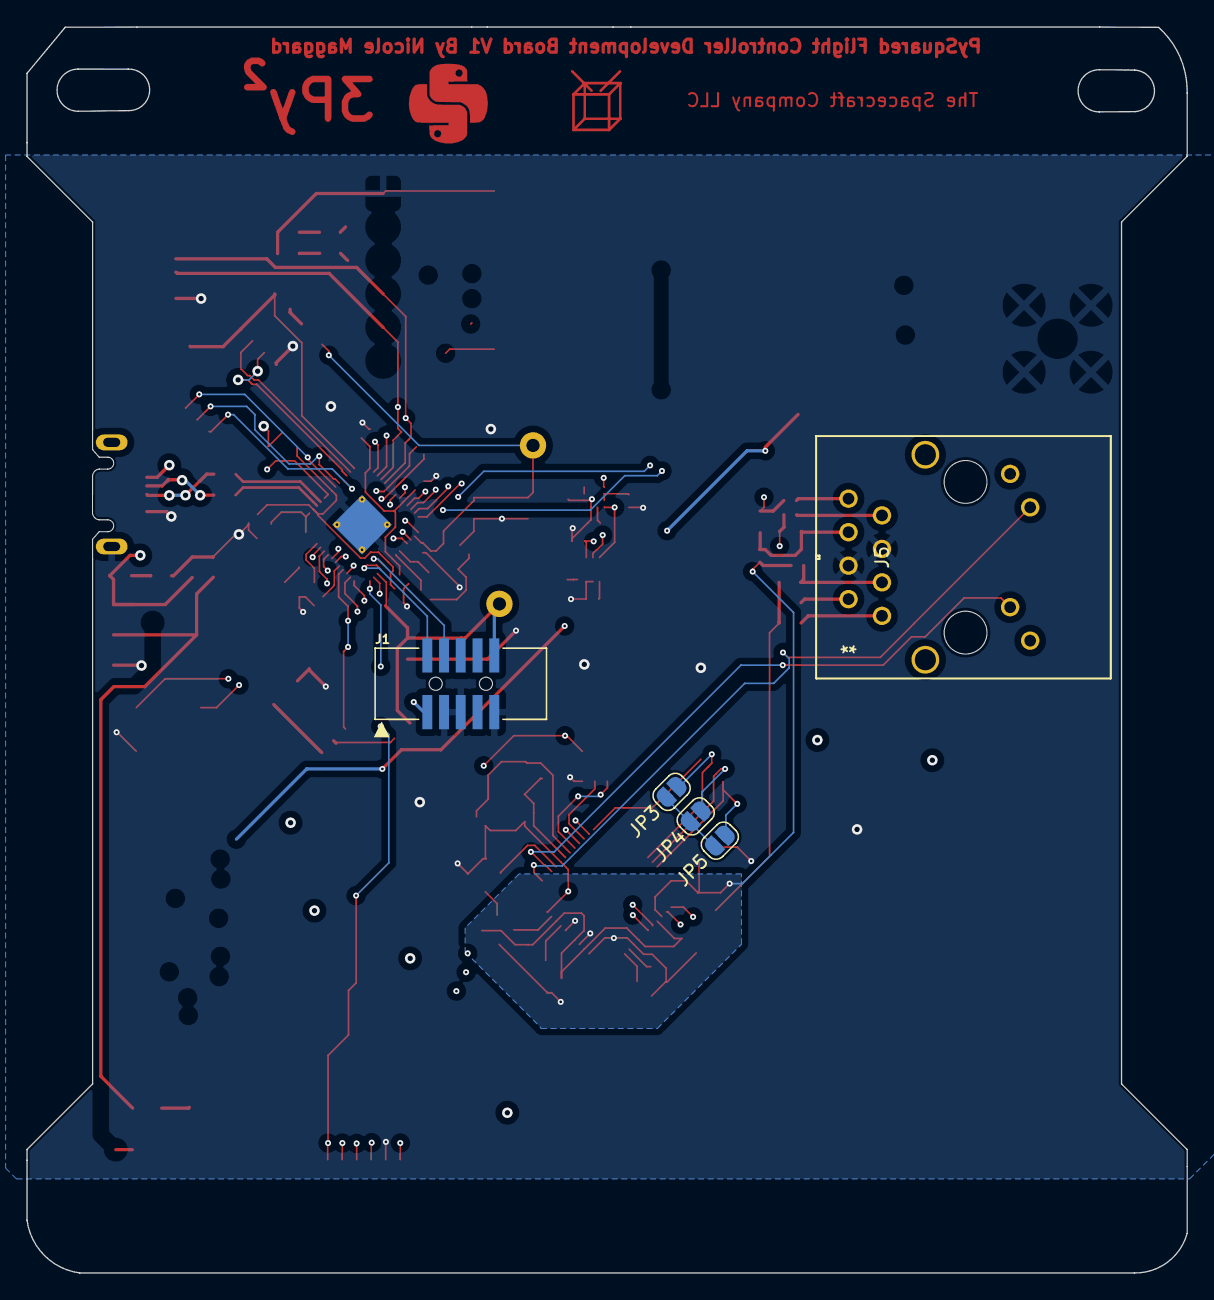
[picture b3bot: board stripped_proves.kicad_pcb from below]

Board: 4 copper layers, 88.0 x 94.5 mm, 124 parts (5 on the bottom side), 84 nets.

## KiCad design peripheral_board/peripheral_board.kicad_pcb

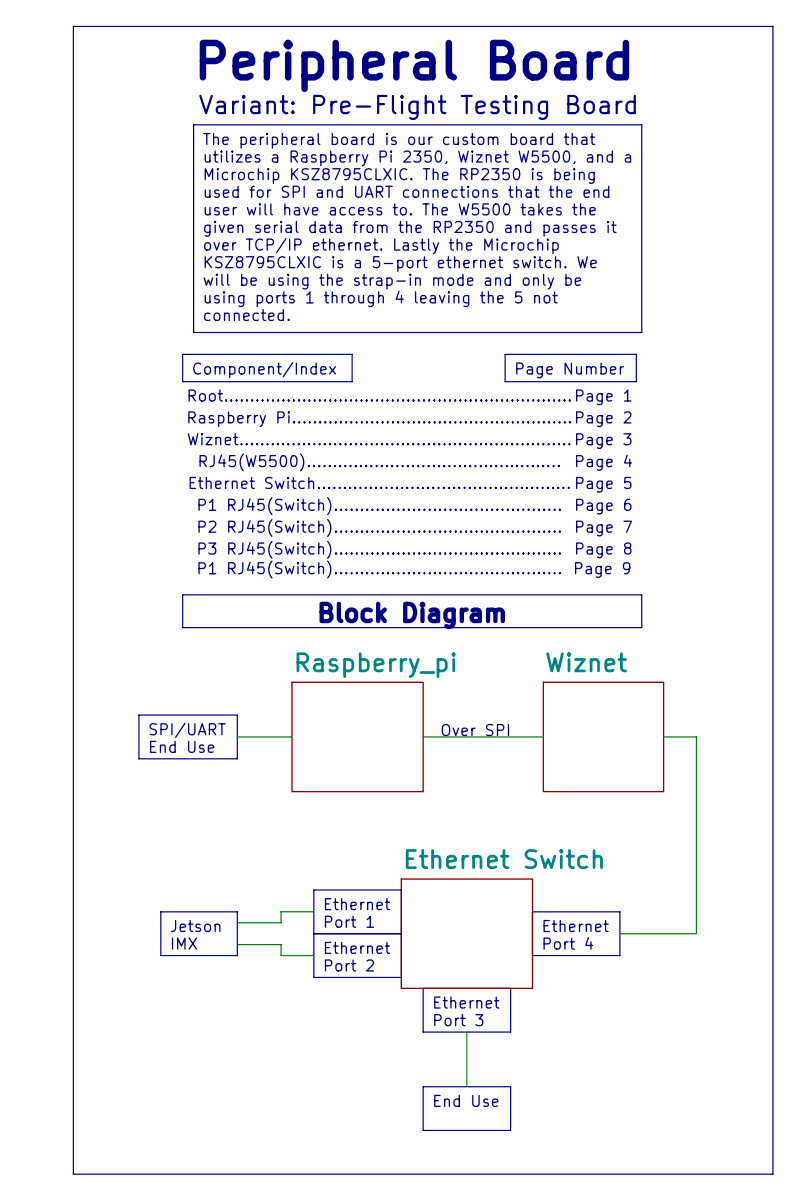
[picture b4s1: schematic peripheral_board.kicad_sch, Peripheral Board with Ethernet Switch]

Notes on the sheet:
Page 2
Page 1
Wiznet................................................................
Page 4
Page 8
Page 5
Page 6
P3 RJ45(Switch)............................................
Peripheral Board
P1 RJ45(Switch)............................................
RJ45(W5500).................................................
Ethernet Switch.................................................
Page 3
P2 RJ45(Switch)............................................
Root...................................................................
Raspberry Pi......................................................
Page 7
Over SPI
Variant: Pre-Flight Testing Board
Page 9
Ethernet Port 2
Component/Index
Page Number
Block Diagram
Jetson IMX
Ethernet Port 1
SPI/UART End Use
The peripheral board is our custom board that utilizes a Raspberry Pi 2350, Wiznet W5500, and a Microchip KSZ8795CLXIC. The RP2350 is being used for SPI and UART connections that the end user will have access to. The W5500 takes the given serial data from the RP2350 and passes it over TCP/IP ethern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
Ethernet Port 3
End Use
Ethernet Port 4
